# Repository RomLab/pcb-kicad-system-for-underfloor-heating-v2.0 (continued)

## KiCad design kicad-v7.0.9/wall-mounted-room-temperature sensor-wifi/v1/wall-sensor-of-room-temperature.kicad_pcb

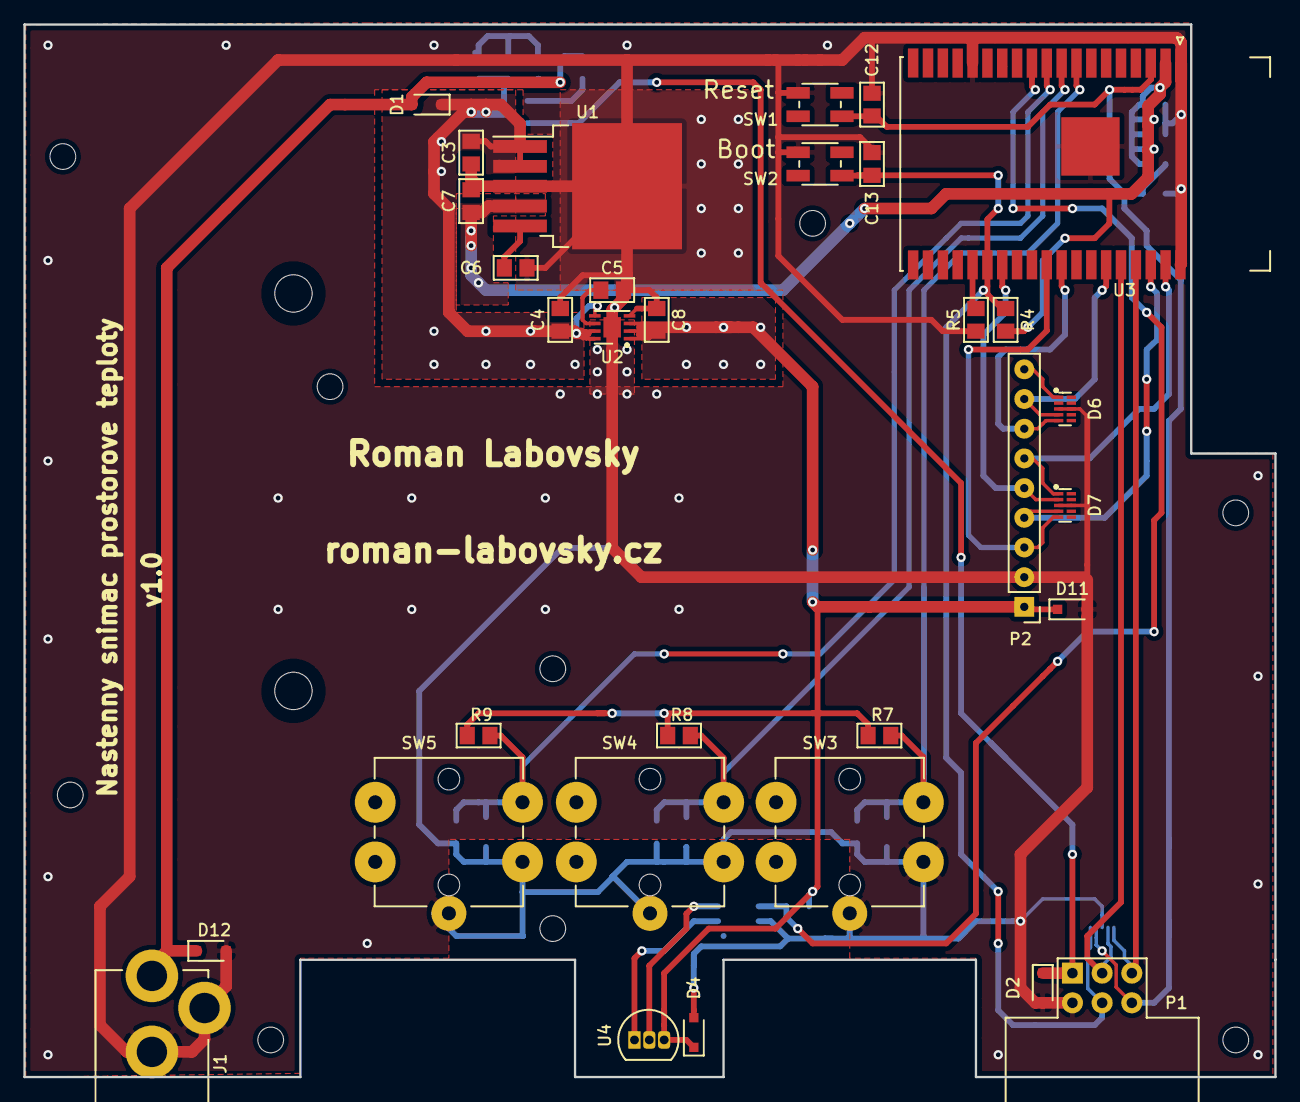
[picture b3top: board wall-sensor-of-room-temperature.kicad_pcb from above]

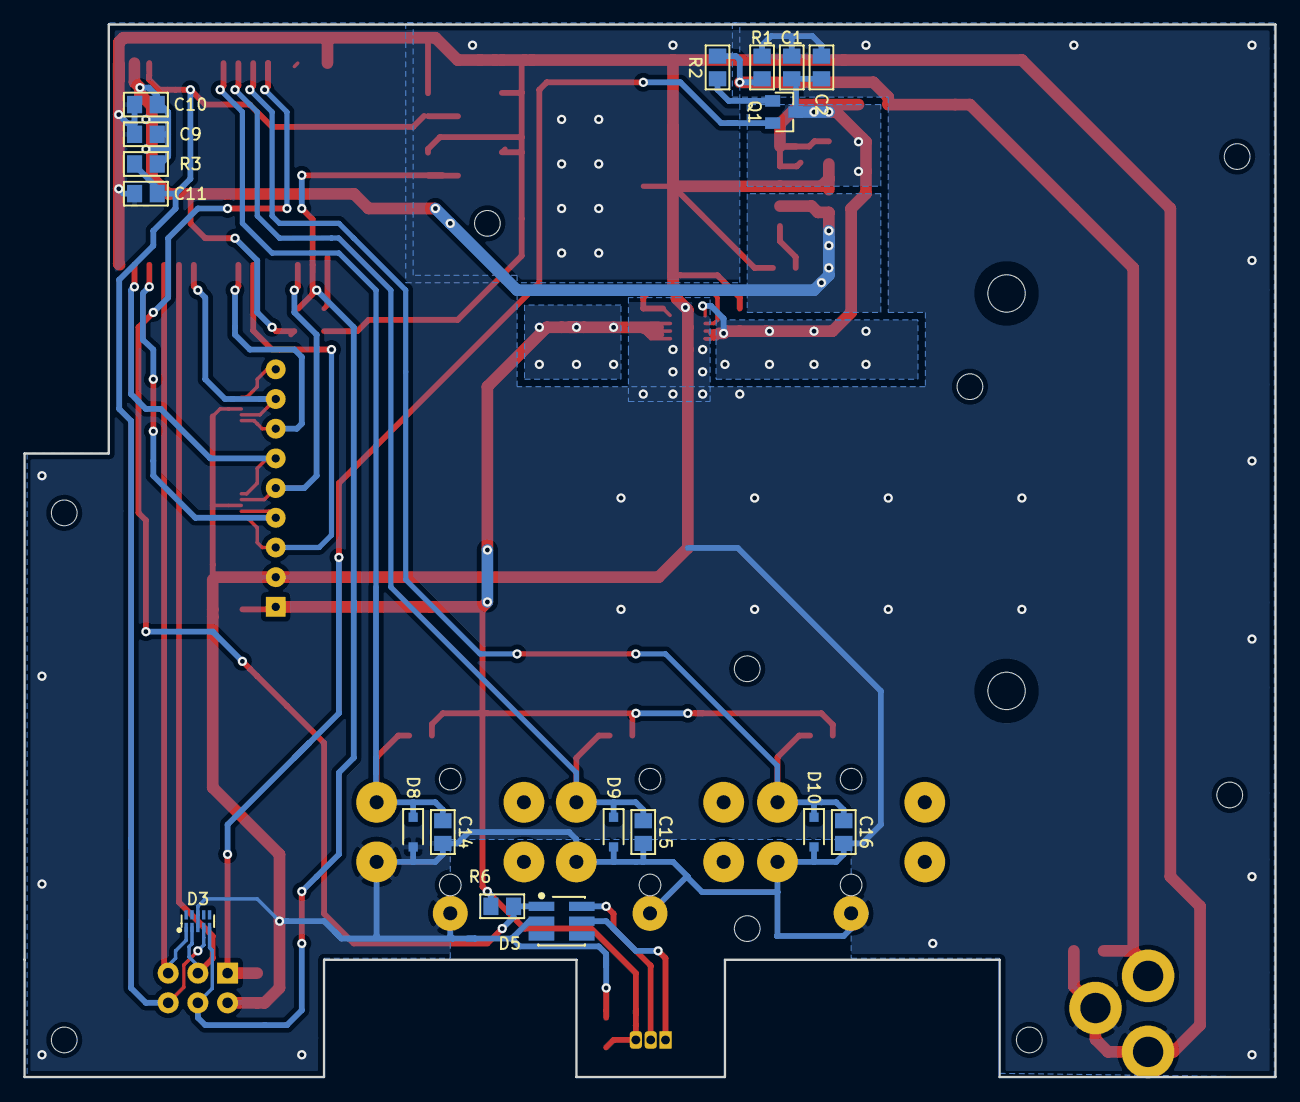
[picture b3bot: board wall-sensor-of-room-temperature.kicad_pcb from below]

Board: 2 copper layers, 107.0 x 90.0 mm, 50 parts (18 on the bottom side), 27 nets.

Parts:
C1: 22uF/25V; c_0805
C2: 1uF/16V; c_0805
C3, C4: 2.2uF/16V; c_0805
C5, C6: 10nF/16V; c_0805
C7, C8: 10uF/16V; c_0805
C9: 22uF; c_0805
C10, C12, C13, C14, C15, C16: 100nF; c_0805
C11: 1uF; c_0805
D1: BAT60B; sod_323
D2, D4, D8, D9, D10, D11, D12: SD05.TCT; sod_323
D3, D6, D7: PHDMI2AB4Z; dfn_2510a_10
D5: DS9503_us; tsoc_6
J1: dc_barrel_jack; PC-GK2.1
P1: 2x3_pins_header; 2x3_pin_header_MLW06A
P2: 1x9_pin_header; 1x9_v_pin_header
Q1: DMG2307L; sot_23_3
R1, R2: 100k; r_0805
R3, R4, R5, R7, R8, R9: 10k; r_0805
R6: 4,7k; r_0805
SW1, SW2: TVAF18BB
SW3, SW4, SW5: B3F-4150
U1: TPS79633KTTR; to_263_5
U2: TPS7A8033DRBR; son_8
U3: ESP32-WROVER-IE
U4: DS18B20; to_92_in_line

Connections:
+5V: C1.1, C2.1, C3.1, C4.1, D1.1, Q1.3, U1.1, U1.2, U2.5, U2.7, U2.8
/1wire_data: D5.1, R6.2, U3.11
/DISPLAY_CLK: D6.5, P2.7, U3.30
/DISPLAY_CS: D7.5, P2.3, U3.29
/DISPLAY_DCRS: D7.2, P2.5, U3.26
/DISPLAY_LED: D6.4, P2.8, U3.33
/DISPLAY_MOSI: D7.1, P2.6, U3.37
/DISPLAY_RST: D7.4, P2.4, U3.36
/EN: C11.1, C12.1, D3.4, P1.6, R3.2, SW1.1, U3.3
/IO0: C13.1, D3.5, P1.4, R4.2, SW2.1, U3.25
/NOT_CONNECTED: D6.1, P2.9
/RXD: D3.2, P1.3, U3.34
/TXD: D3.1, P1.5, U3.35
/button1: C14.1, D8.1, R7.2, SW3.3, U3.8
/button2: C15.1, D9.1, R8.2, SW4.3, U3.9
/button3: C16.1, D10.1, R9.2, SW5.3, U3.10
GND: C1.2, C2.2, C3.2, C4.2, C5.2, C6.2, C7.2, C8.2, C9.2, C10.2, C11.2, C12.2, C13.2, C14.2, C15.2, C16.2, D2.2, D3.3, D3.8, D4.2, D5.2, D6.3, D6.8, D7.3, D7.8, D8.2, D9.2, D10.2, D11.2, D12.2, J1.2, J1.3, P1.2, P2.2, R1.2, R5.2, SW1.4, SW2.4, SW3.1, SW3.5, SW4.1, SW4.5, SW5.1, SW5.5, U1.3, U2.4, U2.9, U3.1, U3.15, U3.38, U3.39
unnamed: C5.1, U2.6
unnamed: C6.1, U1.5
unnamed: D5.5, U4.1
unnamed: D5.6, U4.2
unnamed: Q1.1, R2.2
unnamed: R5.1, U3.24
OTHER_+3,3V: C8.1, D4.1, D11.1, P2.1, R6.1, R7.1, R8.1, R9.1, U2.1, U2.2, U2.3, U4.3
SYS_+3,3V: C7.1, C9.1, C10.1, R3.1, R4.1, U1.4, U3.2
USB_+5V: D2.1, P1.1, Q1.2
VDC: D1.2, D12.1, J1.1, R1.1, R2.1

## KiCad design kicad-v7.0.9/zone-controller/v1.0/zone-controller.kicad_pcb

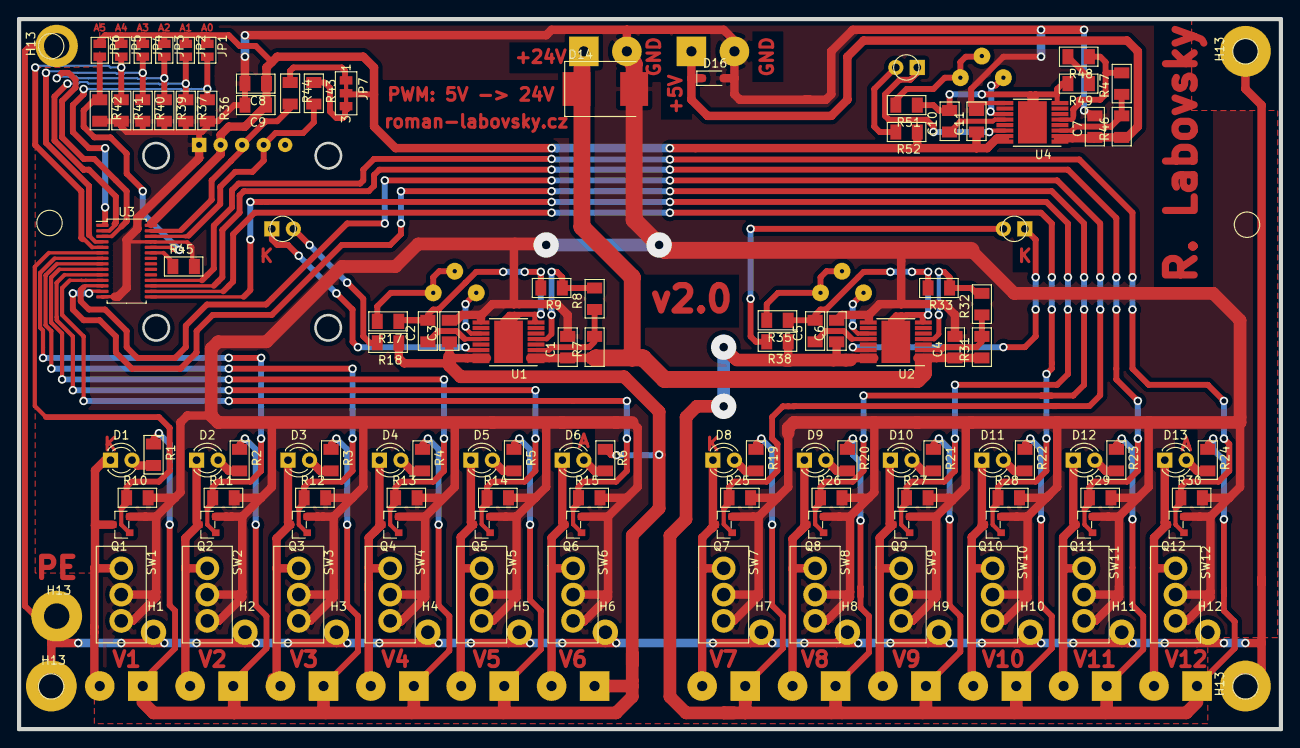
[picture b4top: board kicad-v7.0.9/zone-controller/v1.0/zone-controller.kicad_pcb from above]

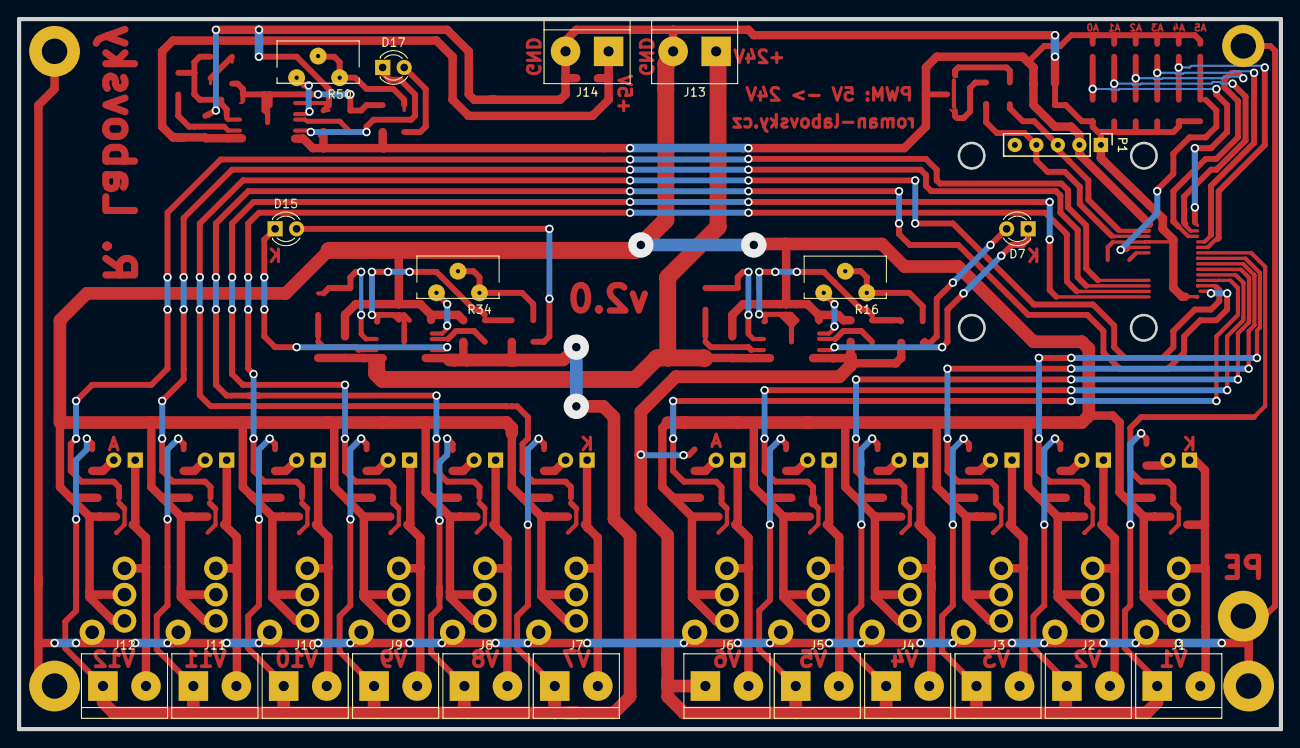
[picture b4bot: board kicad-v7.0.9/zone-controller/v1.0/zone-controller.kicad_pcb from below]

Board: 2 copper layers, 149.0 x 83.8 mm, 147 parts (21 on the bottom side), 79 nets.

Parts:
C1, C3, C4, C6, C7, C11: 1u; c_1206_rl
C2, C5, C10: 1,2n; c_1206_rl
C8: 10u; c_1206_rl
C9: 100n; c_1206_rl
D1, D2, D3, D4, D5, D6, D8, D9, D10, D11, D12, D13: LTL-42NGY8D; led_d3.0mm_rl
D7, D15, D17: LTL-42NEW8D; led_d3.0mm_rl
D14: SMCJ24A; smc_do-214ab_rl
D16: UCLAMP0501H.TCT; sod_323_rl
H1, H2, H3, H4, H5, H6, H7, H8, H9, H10, H11, H12, H13, H13#2, H13#3, H13#4, H13#5: MountingHole_Pad; mountig_hole_3mm_1,6mm_pad
J1, J2, J3, J4, J5, J6, J7, J8, J9, J10, J11, J12: EBBA-02-C-SS-BU; xy301v_a_5_2p_rl
J13, J14: 1x2_screw_term_block; xy301v_a_5_2p_rl
JP1, JP2, JP3, JP4, JP5, JP6: solder_jumper_2_open; solder_jumper_2_open_rect_1x1,5mm
JP7: SolderJumper_3_Bridged123; solder_jumper_3_bridge_rect_1x1,5mm
P1: 1x5_pin_header
Q1, Q2, Q3, Q4, Q5, Q6, Q7, Q8, Q9, Q10, Q11, Q12: DMN3023L-7; sot_23_rl
R1, R2, R3, R4, R5, R6, R19, R20, R21, R22, R23, R24: 2,2k; r_1206_rl
R7, R31: 470K; r_1206_rl
R8, R32: 39k; r_1206_rl
R9, R33: 24K; r_1206_rl
R10, R11, R12, R13, R14, R15, R25, R26, R27, R28, R29, R30, R36, R37, R39, R40, R41, R42, R45: 10k; r_1206_rl
R16, R34, R50: 200K; trimer_t93yb_rl
R17, R35, R51: 5K36; r_1206_rl
R18, R38: 4K3; r_1206_rl
R43, R44: 4k7; r_1206_rl
R46: 100K; r_1206_rl
R47: 3K16; r_1206_rl
R48: 30K; r_1206_rl
R49: 200; r_1206_rl
R52: 604; r_1206_rl
SW1, SW2, SW3, SW4, SW5, SW6, SW7, SW8, SW9, SW10, SW11, SW12: B144; b144_rl
U1, U2, U4: TPS26600; htssop_16_6,6mm×5,1mm
U3: PCA9685PW; TSSOP-28_4.4x9.7mm_P0.65mm

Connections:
+5V: C7.1, D16.1, J14.1, R46.1, U4.1, U4.2
+24V: C1.1, C4.1, D14.1, J13.1, R7.1, R31.1, U1.1, U1.2, U2.1, U2.2
+24V_A: C3.1, J1.1, J2.1, J3.1, J4.1, J5.1, J6.1, R1.1, R2.1, R3.1, R4.1, R5.1, R6.1, R18.1, U1.15, U1.16
+24V_B: C6.1, J7.1, J8.1, J9.1, J10.1, J11.1, J12.1, R19.1, R20.1, R21.1, R22.1, R23.1, R24.1, R38.1, U2.15, U2.16
/a0: JP1.2, R36.1, U3.1
/a1: JP2.2, R37.1, U3.2
/a2: JP3.2, R39.1, U3.3
/a3: JP4.2, R40.1, U3.4
/a4: JP5.2, R41.1, U3.5
/a5: JP6.2, R42.1, U3.24
/led0: Q1.1, R10.1, U3.6
/led1: Q2.1, R11.1, U3.7
/led2: Q3.1, R12.1, U3.8
/led3: Q4.1, R13.1, U3.9
/led4: Q5.1, R14.1, U3.10
/led5: Q6.1, R15.1, U3.11
/led6: Q7.1, R25.1, U3.12
/led7: Q8.1, R26.1, U3.13
/led8: Q9.1, R27.1, U3.15
/led9: Q10.1, R28.1, U3.16
/led10: Q11.1, R29.1, U3.17
/led11: Q12.1, R30.1, U3.18
/scl: P1.4, R43.2, U3.26
/sda: P1.3, R44.2, U3.27
/vdd: C8.1, C9.1, C11.1, JP1.1, JP2.1, JP3.1, JP4.1, JP5.1, JP6.1, JP7.2, P1.2, R52.1, U3.28, U4.15, U4.16
Earth_Protective: H1.1, H2.1, H3.1, H4.1, H5.1, H6.1, H7.1, H8.1, H9.1, H10.1, H11.1, H12.1, H13.1, H13#2.1, H13#3.1, H13#4.1, H13#5.1
GND: C1.2, C3.2, C4.2, C6.2, C7.2, C8.2, C9.2, C11.2, D14.2, D16.2, J13.2, J14.2, P1.1, Q1.2, Q2.2, Q3.2, Q4.2, Q5.2, Q6.2, Q7.2, Q8.2, Q9.2, Q10.2, Q11.2, Q12.2, R10.2, R11.2, R12.2, R13.2, R14.2, R15.2, R25.2, R26.2, R27.2, R28.2, R29.2, R30.2, R36.2, R37.2, R39.2, R40.2, R41.2, R42.2, R45.2, SW1.2, SW1.3, SW2.2, SW2.3, SW3.2, SW3.3, SW4.2, SW4.3, SW5.2, SW5.3, SW6.2, SW6.3, SW7.2, SW7.3, SW8.2, SW8.3, SW9.2, SW9.3, SW10.2, SW10.3, SW11.2, SW11.3, SW12.2, SW12.3, U1.9, U2.9, U3.14, U3.25, U4.9
unnamed: C2.1, U1.12
unnamed: C2.2, R9.2, R17.1, U1.8
unnamed: C5.1, U2.12
unnamed: C5.2, R33.2, R35.1
unnamed: C10.1, U4.12
unnamed: C10.2, R49.2, R51.1
unnamed: D1.1, J1.2, Q1.3, SW1.1
unnamed: D1.2, R1.2
unnamed: D2.1, J2.2, Q2.3, SW2.1
unnamed: D2.2, R2.2
unnamed: D3.1, J3.2, Q3.3, SW3.1
unnamed: D3.2, R3.2
unnamed: D4.1, J4.2, Q4.3, SW4.1
unnamed: D4.2, R4.2
unnamed: D5.1, J5.2, Q5.3, SW5.1
unnamed: D5.2, R5.2
unnamed: D6.1, J6.2, Q6.3, SW6.1
unnamed: D6.2, R6.2
unnamed: D7.1, U1.14
unnamed: D7.2, R18.2
unnamed: D8.1, J7.2, Q7.3, SW7.1
unnamed: D8.2, R19.2
unnamed: D9.1, J8.2, Q8.3, SW8.1
unnamed: D9.2, R20.2
unnamed: D10.1, J9.2, Q9.3, SW9.1
unnamed: D10.2, R21.2
unnamed: D11.1, J10.2, Q10.3, SW10.1
unnamed: D11.2, R22.2
unnamed: D12.1, J11.2, Q11.3, SW11.1
unnamed: D12.2, R23.2
unnamed: D13.1, J12.2, Q12.3, SW12.1
unnamed: D13.2, R24.2
unnamed: D15.1, U2.14
unnamed: D15.2, R38.2
unnamed: D17.1, U4.14
unnamed: D17.2, R52.2
unnamed: JP7.1, R44.1
unnamed: JP7.3, R43.1
unnamed: R7.2, R8.1, U1.3
unnamed: R8.2, R9.1, U1.5
unnamed: R16.1, U1.11
unnamed: R16.2, R16.3, R17.2
unnamed: R31.2, R32.1, U2.3
unnamed: R32.2, R33.1, U2.5
unnamed: R34.1, U2.11
unnamed: R34.2, R34.3, R35.2
unnamed: R45.1, U3.23
unnamed: R46.2, R47.1, U4.3
unnamed: R47.2, R48.1, U4.5
unnamed: R48.2, R49.1
unnamed: R50.1, U4.11
unnamed: R50.2, R50.3, R51.2

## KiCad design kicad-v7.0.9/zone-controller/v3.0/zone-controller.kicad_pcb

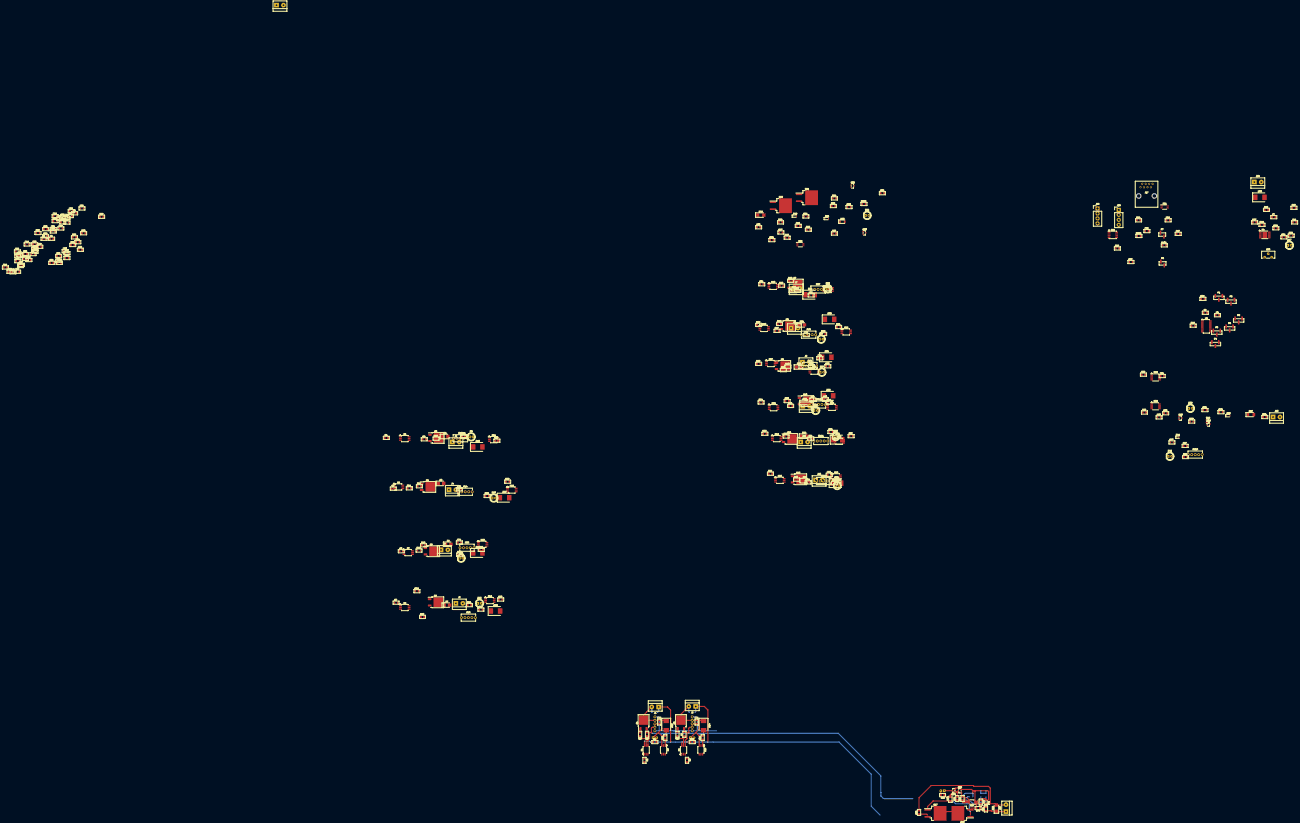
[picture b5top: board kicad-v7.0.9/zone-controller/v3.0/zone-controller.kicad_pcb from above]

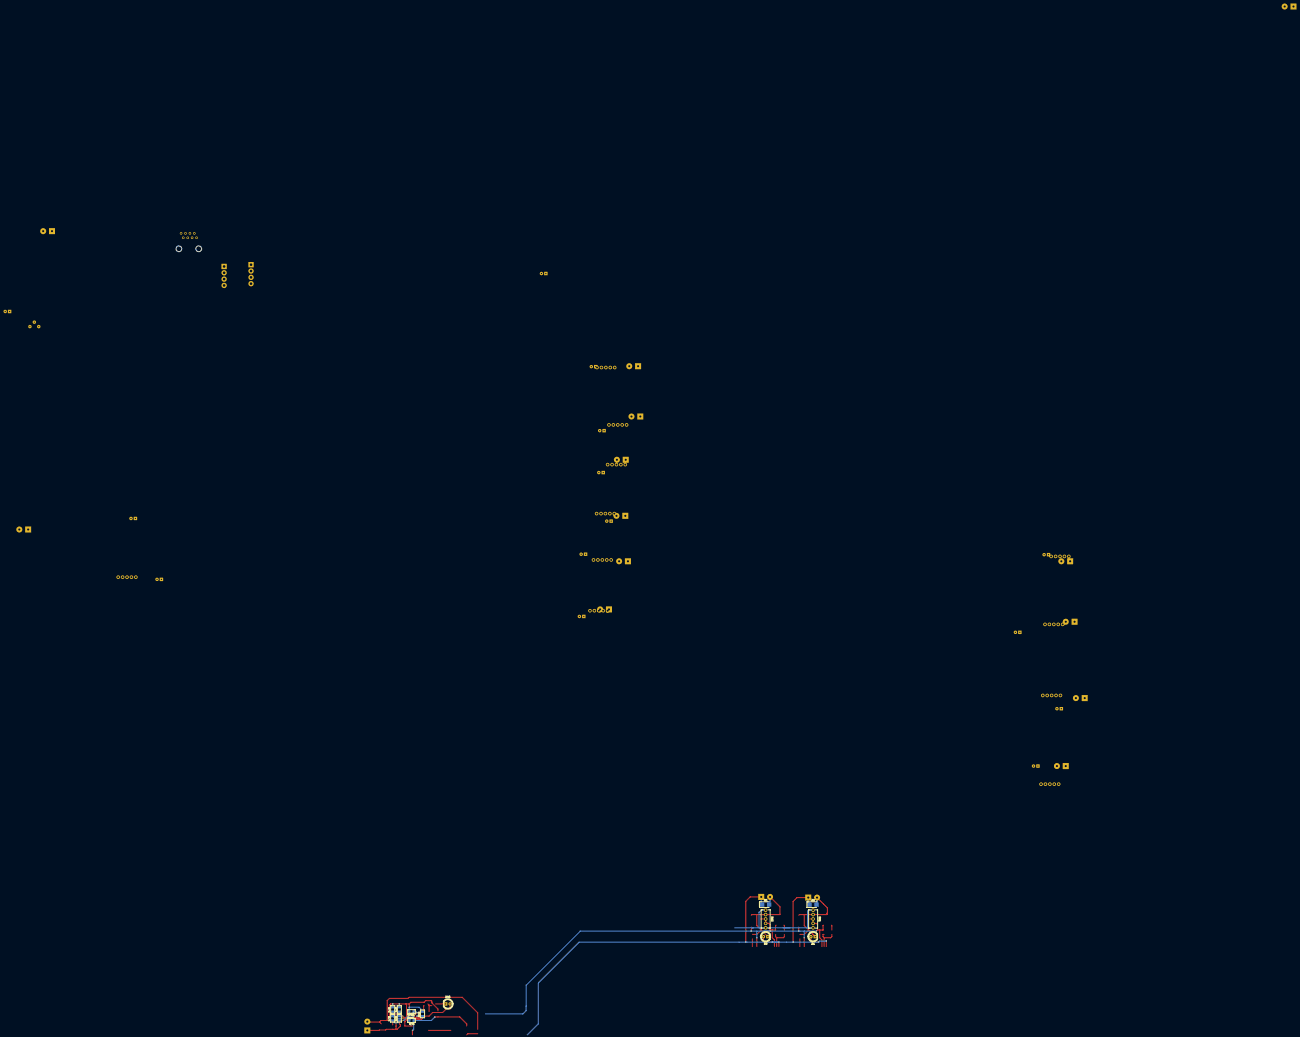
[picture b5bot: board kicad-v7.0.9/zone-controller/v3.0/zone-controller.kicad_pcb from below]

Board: 2 copper layers, 332 parts (15 on the bottom side), 173 nets.

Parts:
C1, C2, C3, C9, C12, C13, C14, C18, C19, C20, C24, C25, C26, C30, C31, C32, C36, C37, C38, C42, C43, C44, C48, C49, C50, C57, C59, C60, C67, C68, C71, C72, C73, C74, C75, C76, C77, C78, C79, C80, C81, C82: 100nF; c_1206
C4, C5, C6, C7, C11, C15, C16, C17, C21, C22, C23, C27, C28, C29, C33, C34, C35, C39, C40, C41, C45, C46, C47, C51, C52, C53, C61, C62, C66, C70: 1uF; c_1206
C8, C54, C58, C63, C69: 10uF; c_1206
C10: 1.2nF; c_1206
C55, C64: 1000pF; c_1206
C56, C65: 33nF; c_1206
D1, D8, D9, D10, D11, D12, D26, D27, D28, D29, D30, D31, D38, D42: LL-504PGC1E-G5-2B; led_d5mm_2.54mm
D2, D3, D4, D5, D6, D7, D20, D21, D22, D23, D24, D25: STPS160A; sma
D13, D14, D15, D16, D18, D19, D32, D33, D34, D35, D36, D37: SMCJ24A-CD; smc
D17, D45, D54: LL-503VC1E-4C; led_d5mm_2.54mm
D39, D48: SMBJ24CA-TR; smb
D40, D41, D49, D51: BAV20WS-DC; sod_323
D43, D53: TZMB27-GS08; minimelf_sod_80
D44: UCLAMP0501H.TCT; sod_523
D46: SD05-7; sod_323
D47: PMEG40T30EPX; sod_128
D50: SMCJ5.0CA-13-F; smc
D52: SMDA05CDR2G; soic_8_3.9mmx4.9mm
J1, J2, J3, J4, J5, J6, J7, J8, J9, J10, J11, J12, J13, J14, J15, J19: EBBA-02-C-SS-BU
J16, J18: 1x4_idc_lsa; 1x4_idc_lsa_connector_general
J17: 54601-908WPLF; rj45_54601-908WPLF
P1, P2, P3, P4, P5, P6: 1x3_pin_header; 1x3_pinheader_2.54mm_vertical
P7, P8: 1x2_pin_header; 1x2_pinheader_2.54mm_vertical
Q1, Q2, Q3, Q4, Q5, Q6, Q7, Q8, Q9, Q10, Q11, Q12: AOD458; to_252_2
Q13, Q14, Q16, Q18, Q19, Q22, Q23: PMV213SN,215; sot_23
Q15, Q17, Q20, Q21: AOB1608L; to_263_2
R1, R20, R21, R22, R23, R24, R57, R58, R59, R60, R61, R62, R83, R102: 2k2/0.5W; r_1206
R2, R3, R4, R5, R6, R7, R31, R32, R33, R34, R35, R36: 1k15; r_1206
R8, R9, R10, R11, R12, R13, R37, R38, R39, R40, R41, R42, R85: NC (10k); r_1206
R14, R15, R16, R17, R18, R19, R43, R44, R53, R54, R55, R56, R72: 1k; r_1206
R25, R26, R27, R28, R29, R30, R63, R64, R65, R66, R67, R68: 7k5; r_1206
R45, R79, R80, R86: 10k; r_1206
R46, R81, R82, R98, R99: 100k; r_1206
R47: 3k16; r_1206
R48: 30k; r_1206
R49: 200R; r_1206
R50: 200k; trimmer_t93yb
R51: 5k36; r_1206
R52: 604R; r_1206
R69: 348R; r_1206
R70, R87: 24k; r_1206
R71, R88: 2k67; r_1206
R73, R89: 47k5; r_1206
R74, R90: 9k76; r_1206
R75, R91: 25m; r_1206
R76, R92: 1M; r_1206
R77: 340R; r_1206
R78, R93: 14k3; r_1206
R84, R94, R95, R96, R97: 10R/0.5W; r_1206
R100, R101: 4k7; r_1206
SW1, SW2, SW3, SW4, SW5, SW6, SW7, SW8, SW9, SW10, SW11, SW12, SW13: SMTS-102-2C2T
U1, U2, U5, U6, U7, U8, U9, U10, U11, U12, U13, U14, U15, U16, U17, U18, U19, U20, U21, U22, U23, U24, U25, U26: TLP2345; so_6
U3: PCA9685PW; tssop_28
U4: TPS26600; htssop_16_6.6mm×5.1mm
U27, U30: LM5069; vssop_10
U28, U29: SN74HCS21-Q1; tssop_14
U?1: PCA9615; vssop_10

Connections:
+5V: C8.1, C9.1, C11.1, C12.1, C13.1, C14.1, C15.1, C16.1, C17.1, C24.1, C25.1, C26.1, C27.1, C28.1, C29.1, C36.1, C37.1, C38.1, C39.1, C40.1, C41.1, C48.1, C49.1, C50.1, C51.1, C52.1, C53.1, C59.2, C60.2, C61.2, C62.2, C66.1, C67.1, C68.1, C70.1, R52.1, R69.1, R72.1, R77.1, R79.1, R80.1, R85.1, R86.1, R100.1, R101.1, U3.28, U4.15, U4.16, U9.6, U10.6, U11.6, U12.6, U13.6, U14.6, U21.6, U22.6, U23.6, U24.6, U25.6, U26.6, U28.14, U29.14, U?1.1, U?1.10
+24V_A: C1.1, C2.1, C3.1, C4.1, C5.1, C6.1, C18.1, C19.1, C20.1, C21.1, C22.1, C23.1, C58.1, D2.1, D3.1, D4.1, D5.1, D6.1, D7.1, J1.1, J2.1, J3.1, J4.1, J5.1, J6.1, Q17.3, R1.1, R20.1, R21.1, R22.1, R23.1, R24.1, U1.6, U2.6, U5.6, U6.6, U7.6, U8.6
+24V_B: C30.1, C31.1, C32.1, C33.1, C34.1, C35.1, C42.1, C43.1, C44.1, C45.1, C46.1, C47.1, C69.1, D20.1, D21.1, D22.1, D23.1, D24.1, D25.1, J7.1, J8.1, J9.1, J10.1, J11.1, J12.1, Q21.3, R57.1, R58.1, R59.1, R60.1, R61.1, R62.1, U15.6, U16.6, U17.6, U18.6, U19.6, U20.6
/A0: P1.2, U3.1
/A1: P2.2, U3.2
/A2: P3.2, U3.3
/A3: P4.2, U3.4
/A4: P5.2, U3.5
/A5: P6.2, U3.24
/AND_OUT_0_3: U28.6, U29.9
/AND_OUT_4_7: U28.8, U29.10
/AND_OUT_8_11: U29.6, U29.12
/AND_OUT_PUMP: Q14.1, R85.2, U29.8
/DSCL_N: D52.4, R97.2, U?1.6
/DSCL_N_CON: J16.1, J17.1, R97.1
/DSCL_P: D52.3, R96.2, U?1.7
/DSCL_P_CON: J16.2, J17.2, R96.1
/DSDA_N: D52.1, R95.2, U?1.9
/DSDA_N_CON: J16.3, J17.7, R95.1
/DSDA_P: D52.2, R94.2, U?1.8
/DSDA_P_CON: J16.4, J17.8, R94.1
/INPUT_24V: C54.1, C55.2, C63.1, C64.2, D39.1, D40.1, D48.1, D49.1, J13.1, R70.1, R73.1, R75.2, R87.1, R89.1, R91.2, U27.2, U30.2
/LED0: R2.2, U3.6
/LED0_5V: U9.5, U28.1
/LED0_24V: C76.2, D1.1, D2.2, D13.1, J1.2, Q1.3, R25.2, SW1.2
/LED1: R3.2, U3.7
/LED1_5V: U10.5, U28.2
/LED1_24V: C71.2, D3.2, D8.1, D14.1, J2.2, Q2.3, R26.2, SW2.2
/LED2: R4.2, U3.8
/LED2_5V: U11.5, U28.4
/LED2_24V: C72.2, D4.2, D9.1, D15.1, J3.2, Q3.3, R27.2, SW3.2
/LED3: R5.2, U3.9
/LED3_5V: U12.5, U28.5
/LED3_24V: C73.2, D5.2, D10.1, D16.1, J4.2, Q4.3, R28.2, SW4.2
/LED4: R6.2, U3.10
/LED4_5V: U13.5, U28.9
/LED4_24V: C74.2, D6.2, D11.1, D18.1, J5.2, Q5.3, R29.2, SW5.2
/LED5: R7.2, U3.11
/LED5_5V: U14.5, U28.10
/LED5_24V: C75.2, D7.2, D12.1, D19.1, J6.2, Q6.3, R30.2, SW6.2
/LED6: R31.2, U3.12
/LED6_5V: U21.5, U28.12
/LED6_24V: C77.2, D20.2, D26.1, D32.1, J7.2, Q7.3, R63.2, SW7.2
/LED7: R32.2, U3.13
/LED7_5V: U22.5, U28.13
/LED7_24V: C78.2, D21.2, D27.1, D33.1, J8.2, Q8.3, R64.2, SW8.2
/LED8: R33.2, U3.15
/LED8_5V: U23.5, U29.1
/LED8_24V: C79.2, D22.2, D28.1, D34.1, J9.2, Q9.3, R65.2, SW9.2
/LED9: R34.2, U3.16
/LED9_5V: U24.5, U29.2
/LED9_24V: C80.2, D23.2, D29.1, D35.1, J10.2, Q10.3, R66.2, SW10.2
/LED10: R35.2, U3.17
/LED10_5V: U25.5, U29.4
/LED10_24V: C81.2, D24.2, D30.1, D36.1, J11.2, Q11.3, R67.2, SW11.2
/LED11: R36.2, U3.18
/LED11_5V: U26.5, U29.5
/LED11_24V: C82.2, D25.2, D31.1, D37.1, J12.2, Q12.3, R68.2, SW12.2
/PUMP_ACTIVE_0: D46.1, D47.2, Q13.1, Q14.3, Q16.1, R72.2
/PUMP_SWITCH: C57.1, D42.1, D44.1, R80.2, SW13.2, U29.13
/SCL: P7.1, U3.26, U?1.4
/SDA: P8.1, U3.27, U?1.2
Earth_Protective: J19.1, J19.2, SW1.1, SW1.5, SW2.1, SW2.5, SW3.1, SW3.5, SW4.1, SW4.5, SW5.1, SW5.5, SW6.1, SW6.5, SW7.1, SW7.5, SW8.1, SW8.5, SW9.1, SW9.5, SW10.1, SW10.5, SW11.1, SW11.5, SW12.1, SW12.5, SW13.1, SW13.5
GND: C7.2, C8.2, C9.2, C11.2, C12.2, C13.2, C14.2, C15.2, C16.2, C17.2, C24.2, C25.2, C26.2, C27.2, C28.2, C29.2, C36.2, C37.2, C38.2, C39.2, C40.2, C41.2, C48.2, C49.2, C50.2, C51.2, C52.2, C53.2, C57.2, C59.1, C60.1, C61.1, C62.1, C66.2, C67.2, C68.2, C70.2, D44.2, D46.2, D50.2, D52.5, D52.6, D52.7, D52.8, J14.2, P1.1, P2.1, P3.1, P4.1, P5.1, P6.1, Q13.2, Q14.2, Q16.2, R45.2, SW13.3, SW13.4, U1.3, U2.3, U3.14, U3.25, U4.9, U5.3, U6.3, U7.3, U8.3, U9.4, U10.4, U11.4, U12.4, U13.4, U14.4, U15.3, U16.3, U17.3, U18.3, U19.3, U20.3, U21.4, U22.4, U23.4, U24.4, U25.4, U26.4, U28.7, U29.7, U?1.5
GND1: C55.1, C56.2, D41.2, D43.2, Q18.2, Q19.2, R71.2, R74.2, R78.2, U27.5
GND2: C64.1, C65.2, D51.2, D53.2, Q22.2, Q23.2, R88.2, R90.2, R93.2, U30.5
GND_A: C1.2, C2.2, C3.2, C4.2, C5.2, C6.2, C18.2, C19.2, C20.2, C21.2, C22.2, C23.2, C30.2, C31.2, C32.2, C33.2, C34.2, C35.2, C42.2, C43.2, C44.2, C45.2, C46.2, C47.2, C54.2, C58.2, C63.2, C69.2, C71.1, C72.1, C73.1, C74.1, C75.1, C76.1, C77.1, C78.1, C79.1, C80.1, C81.1, C82.1, D13.2, D14.2, D15.2, D16.2, D18.2, D19.2, D32.2, D33.2, D34.2, D35.2, D36.2, D37.2, D39.2, D41.1, D48.2, D51.1, J13.2, Q1.2, Q2.2, Q3.2, Q4.2, Q5.2, Q6.2, Q7.2, Q8.2, Q9.2, Q10.2, Q11.2, Q12.2, R8.2, R9.2, R10.2, R11.2, R12.2, R13.2, R37.2, R38.2, R39.2, R40.2, R41.2, R42.2, SW1.3, SW1.4, SW2.3, SW2.4, SW3.3, SW3.4, SW4.3, SW4.4, SW5.3, SW5.4, SW6.3, SW6.4, SW7.3, SW7.4, SW8.3, SW8.4, SW9.3, SW9.4, SW10.3, SW10.4, SW11.3, SW11.4, SW12.3, SW12.4, U1.4, U2.4, U5.4, U6.4, U7.4, U8.4, U9.3, U10.3, U11.3, U12.3, U13.3, U14.3, U15.4, U16.4, U17.4, U18.4, U19.4, U20.4, U21.3, U22.3, U23.3, U24.3, U25.3, U26.3
unnamed: C7.1, D50.1, J14.1, R46.1, U4.1, U4.2
unnamed: C10.1, U4.12
unnamed: C10.2, R49.2, R51.1
unnamed: C56.1, U27.6
unnamed: C65.1, U30.6
unnamed: D1.2, R1.2
unnamed: D8.2, R20.2
unnamed: D9.2, R21.2
unnamed: D10.2, R22.2
unnamed: D11.2, R23.2
unnamed: D12.2, R24.2
unnamed: D17.1, U4.14
unnamed: D17.2, R52.2
unnamed: D26.2, R57.2
unnamed: D27.2, R58.2
unnamed: D28.2, R59.2
unnamed: D29.2, R60.2
unnamed: D30.2, R61.2
unnamed: D31.2, R62.2
unnamed: D38.1, Q13.3
unnamed: D38.2, R69.2
unnamed: D40.2, R76.2
unnamed: D42.2, R77.2
unnamed: D43.1, Q15.1, Q17.1, R76.1, U27.10
unnamed: D45.1, Q19.3
unnamed: D45.2, R83.2
unnamed: D47.1, R84.2
unnamed: D49.2, R92.2
unnamed: D53.1, Q20.1, Q21.1, R92.1, U30.10
unnamed: D54.1, Q23.3
unnamed: D54.2, R102.2
unnamed: J15.1, J15.2, R84.1
unnamed: P1.3, P2.3, P3.3, P4.3, P5.3, P6.3, R86.2
unnamed: P7.2, R100.2
unnamed: P8.2, R101.2
unnamed: Q1.1, R14.1
unnamed: Q2.1, R15.1
unnamed: Q3.1, R16.1
unnamed: Q4.1, R17.1
unnamed: Q5.1, R18.1
unnamed: Q6.1, R19.1
unnamed: Q7.1, R43.1
unnamed: Q8.1, R44.1
unnamed: Q9.1, R53.1
unnamed: Q10.1, R54.1
unnamed: Q11.1, R55.1
unnamed: Q12.1, R56.1
unnamed: Q15.2, Q17.2
unnamed: Q15.3, R75.1, U27.1
unnamed: Q16.3, R79.2
unnamed: Q18.1, R81.2, U27.8
unnamed: Q18.3, Q19.1, R82.2
unnamed: Q20.2, Q21.2
unnamed: Q20.3, R91.1, U30.1
unnamed: Q22.1, R98.2, U30.8
unnamed: Q22.3, Q23.1, R99.2
unnamed: R2.1, U1.1
unnamed: R3.1, U2.1
unnamed: R4.1, U5.1
unnamed: R5.1, U6.1
unnamed: R6.1, U7.1
unnamed: R7.1, U8.1
unnamed: R10.1, R14.2, U1.5
unnamed: R11.1, R17.2, U6.5
unnamed: R12.1, R18.2, U7.5
unnamed: R13.1, R19.2, U8.5
unnamed: R8.1, R15.2, U2.5
unnamed: R9.1, R16.2, U5.5
unnamed: R25.1, U9.1
unnamed: R26.1, U10.1
unnamed: R27.1, U11.1
unnamed: R28.1, U12.1
unnamed: R29.1, U13.1
unnamed: R30.1, U14.1
unnamed: R31.1, U15.1
unnamed: R32.1, U16.1
unnamed: R33.1, U17.1
unnamed: R34.1, U18.1
unnamed: R35.1, U19.1
unnamed: R36.1, U20.1
unnamed: R37.1, R44.2, U16.5
unnamed: R38.1, R53.2, U17.5
unnamed: R39.1, R54.2, U18.5
unnamed: R40.1, R55.2, U19.5
unnamed: R41.1, R56.2, U20.5
unnamed: R42.1, R43.2, U15.5
unnamed: R45.1, U3.23
unnamed: R46.2, R47.1, U4.3
unnamed: R47.2, R48.1, U4.5
unnamed: R48.2, R49.1
unnamed: R50.1, R50.2, R51.2
unnamed: R50.3, U4.11
unnamed: R63.1, U21.1
unnamed: R64.1, U22.1
unnamed: R65.1, U23.1
unnamed: R66.1, U24.1
unnamed: R67.1, U25.1
unnamed: R68.1, U26.1
unnamed: R70.2, R71.1, U27.4
unnamed: R73.2, R74.1, U27.3
unnamed: R78.1, U27.7
unnamed: R81.1, R82.1, R83.1, U27.9
unnamed: R87.2, R88.1, U30.4
unnamed: R89.2, R90.1, U30.3
unnamed: R93.1, U30.7
unnamed: R98.1, R99.1, R102.1, U30.9
